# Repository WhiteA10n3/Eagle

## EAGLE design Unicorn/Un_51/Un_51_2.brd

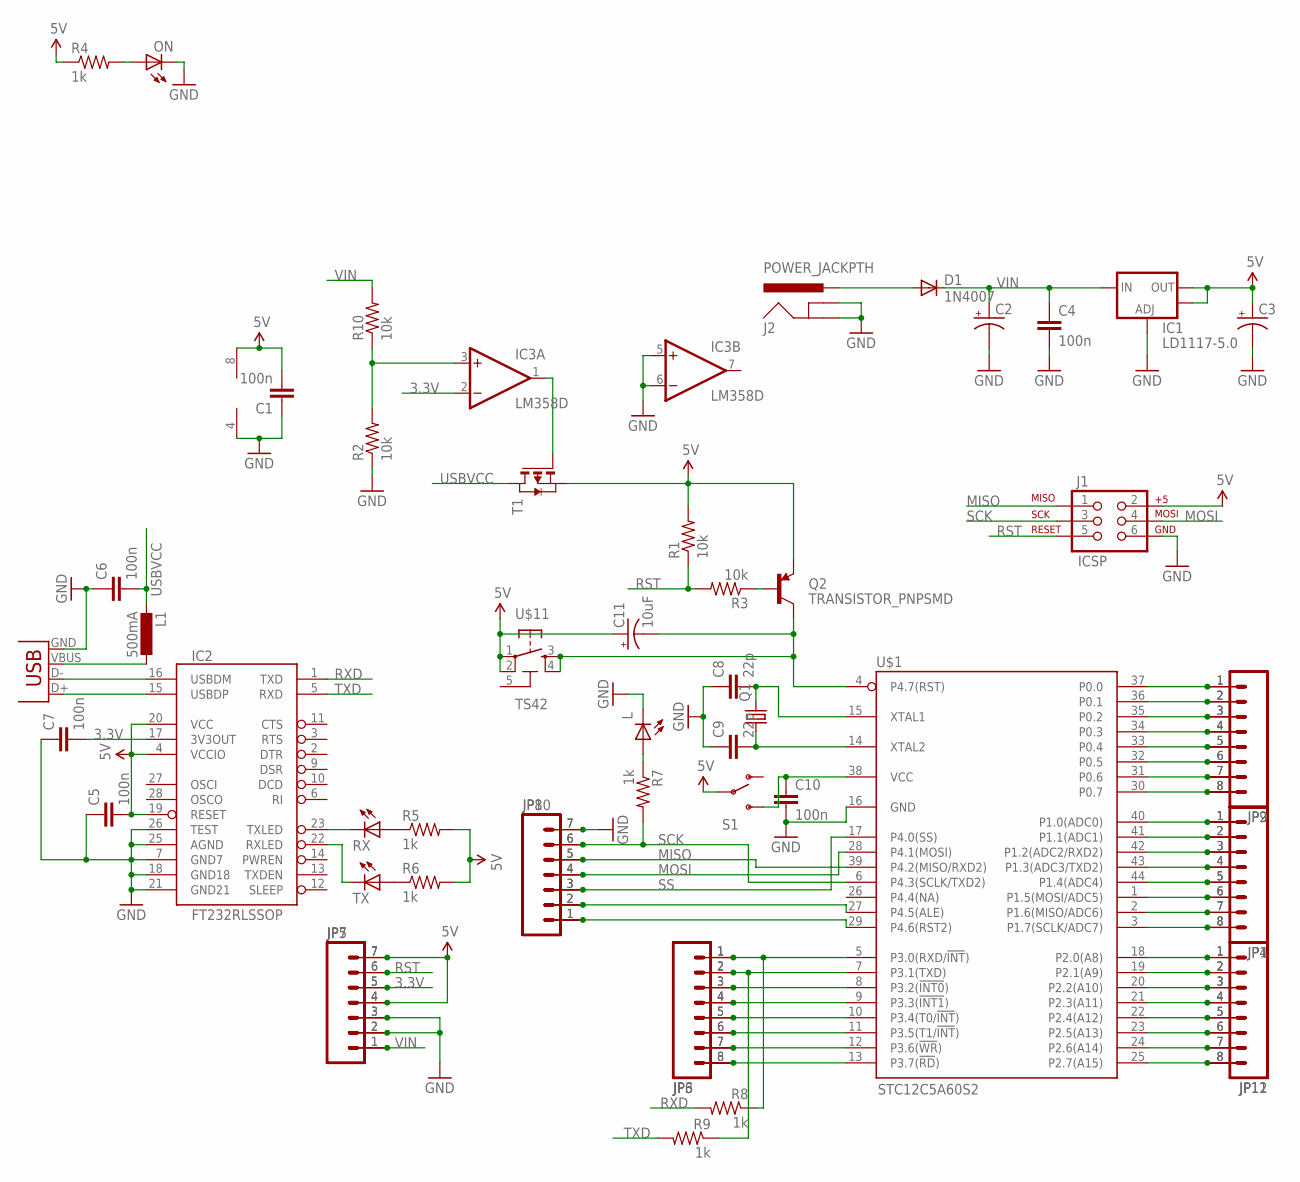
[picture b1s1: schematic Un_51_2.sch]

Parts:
C1, C4, C5, C6, C7, C10: 100n; 0603-CAP
C2, C3: CAP_POLD; PANASONIC_D
C8, C9: 22p; 0805
C11: 10uF; EIA3216
D1: 1N4007; SMB
IC1: LD1117-5.0; SOT223
IC2: FT232RLSSOP; SSOP28DB
IC3: LM358D; SO08
J1: ICSP; 2X3
J2: POWER_JACKPTH; POWER_JACK_PTH
JP1, JP2, JP4, JP9, JP11, JP12: M081X08; 1X08
JP3, JP6: M08; 1X08
JP5, JP7, JP8, JP10: M07; 1X07
L: LED0805; LED-0805
L1: 500mA; L1812
ON: LED0805; LED-0805
Q1: CRYSTALHC49US; HC49US
Q2: TRANSISTOR_PNPSMD; SOT23-3
R1, R2, R3, R10: 10k; 0805
R4, R5, R6, R7, R8, R9: 1k; 0805
RX: LED0805; LED-0805
S1: SWITCH-SPST; SWITCH-SPDT2
T1: PMOSSOT23; SOT-23
TX: LED0805; LED-0805
U$1: STC12C5A60S2; TQFP44
U$11: TS42
X1: USBPTH; USB-B-PTH

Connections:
3.3V: C7.2, IC2.17 (3V3OUT), IC3.2 (-IN), JP5.5, JP7.5
5V: C1.2, C3.+, C5.2, C11.A (+), IC1.2 (OUT), IC1.4 (OUT), IC2.4 (VCCIO), IC2.19 (RESET), IC2.20 (VCC), IC3.8 (V+), J1.2, JP5.4, JP5.7, JP7.4, JP7.7, Q2.2 (E), R1.2, R4.1, R5.2, R6.2, S1.2, T1.2 (S), U$11.1, U$11.2
A0: JP1.1, JP4.1, U$1.40 (P1.0(ADC0))
GND: C1.1, C2.-, C3.-, C4.2, C5.1, C6.1, C7.1, C8.1, C9.1, C10.2, IC1.1 (ADJ), IC2.7 (GND7), IC2.18 (GND18), IC2.21 (GND21), IC2.25 (AGND), IC2.26 (TEST), IC3.4 (V-), IC3.5 (+IN), IC3.6 (-IN), J1.6, J2.GND, J2.GNDBREAK, JP5.2, JP5.3, JP7.2, JP7.3, JP8.7, JP10.7, L.2 (C), ON.2 (C), R2.1, U$1.16 (GND), X1.GND
MISO: J1.1, JP8.5, JP10.5, U$1.39 (P4.2(MISO/RXD2))
MOSI: J1.4, JP8.4, JP10.4, U$1.28 (P4.1(MOSI))
unnamed: IC3.3 (+IN), R2.2, R10.1
unnamed: IC3.1 (OUT), T1.3 (G)
unnamed: L1.1, X1.VBUS
unnamed: D1.A, J2.PWR
unnamed: IC2.16 (USBDM), X1.D-
unnamed: IC2.15 (USBDP), X1.D+
unnamed: R5.1, RX.1 (A)
unnamed: R6.1, TX.1 (A)
unnamed: IC2.23 (TXLED), RX.2 (C)
unnamed: IC2.22 (RXLED), TX.2 (C)
unnamed: JP3.1, JP6.1, R8.1, U$1.5 (P3.0(RXD/!INT!))
unnamed: JP1.7, JP4.7, U$1.2 (P1.6(MISO/ADC6))
unnamed: JP1.8, JP4.8, U$1.3 (P1.7(SCLK/ADC7))
unnamed: L.1 (A), R7.1
unnamed: C10.1, S1.3 (S), U$1.38 (VCC)
unnamed: JP8.1, JP10.1, U$1.29 (P4.6(RST2))
unnamed: JP8.2, JP10.2, U$1.27 (P4.5(ALE))
unnamed: C11.C (-), Q2.3 (C), U$1.4 (P4.7(RST)), U$11.3, U$11.4
unnamed: Q2.1 (B), R3.1
unnamed: JP2.1, JP9.1, U$1.37 (P0.0)
unnamed: JP2.2, JP9.2, U$1.36 (P0.1)
unnamed: JP3.2, JP6.2, R9.1, U$1.7 (P3.1(TXD))
unnamed: JP3.3, JP6.3, U$1.8 (P3.2(!INT0!))
unnamed: JP3.4, JP6.4, U$1.9 (P3.3(!INT1!))
unnamed: JP3.5, JP6.5, U$1.10 (P3.4(T0/!INT!))
unnamed: JP3.6, JP6.6, U$1.11 (P3.5(T1/!INT!))
unnamed: JP3.7, JP6.7, U$1.12 (P3.6(!WR!))
unnamed: JP3.8, JP6.8, U$1.13 (P3.7(!RD!))
unnamed: JP1.2, JP4.2, U$1.41 (P1.1(ADC1))
unnamed: JP1.3, JP4.3, U$1.42 (P1.2(ADC2/RXD2))
unnamed: JP1.4, JP4.4, U$1.43 (P1.3(ADC3/TXD2))
unnamed: ON.1 (A), R4.2
unnamed: JP2.3, JP9.3, U$1.35 (P0.2)
unnamed: JP2.4, JP9.4, U$1.34 (P0.3)
unnamed: JP2.5, JP9.5, U$1.33 (P0.4)
unnamed: C8.2, Q1.2, U$1.15 (XTAL1)
unnamed: C9.2, Q1.1, U$1.14 (XTAL2)
unnamed: JP2.6, JP9.6, U$1.32 (P0.5)
unnamed: JP2.7, JP9.7, U$1.31 (P0.6)
unnamed: JP2.8, JP9.8, U$1.30 (P0.7)
unnamed: JP11.1, JP12.1, U$1.18 (P2.0(A8))
unnamed: JP11.2, JP12.2, U$1.19 (P2.1(A9))
unnamed: JP11.3, JP12.3, U$1.20 (P2.2(A10))
unnamed: JP11.4, JP12.4, U$1.21 (P2.3(A11))
unnamed: JP11.5, JP12.5, U$1.22 (P2.4(A12))
unnamed: JP11.6, JP12.6, U$1.23 (P2.5(A13))
unnamed: JP11.7, JP12.7, U$1.24 (P2.6(A14))
unnamed: JP11.8, JP12.8, U$1.25 (P2.7(A15))
RST: J1.5, JP5.6, JP7.6, R1.1, R3.2
RXD: IC2.1 (TXD), R8.2
SCK: J1.3, JP8.6, JP10.6, R7.2, U$1.6 (P4.3(SCLK/TXD2))
SCL: JP1.6, JP4.6, U$1.1 (P1.5(MOSI/ADC5))
SDA: JP1.5, JP4.5, U$1.44 (P1.4(ADC4))
SS: JP8.3, JP10.3, U$1.17 (P4.0(SS))
TXD: IC2.5 (RXD), R9.2
USBVCC: C6.2, L1.2, T1.1 (D)
VIN: C2.+, C4.1, D1.C, IC1.3 (IN), JP5.1, JP7.1, R10.2

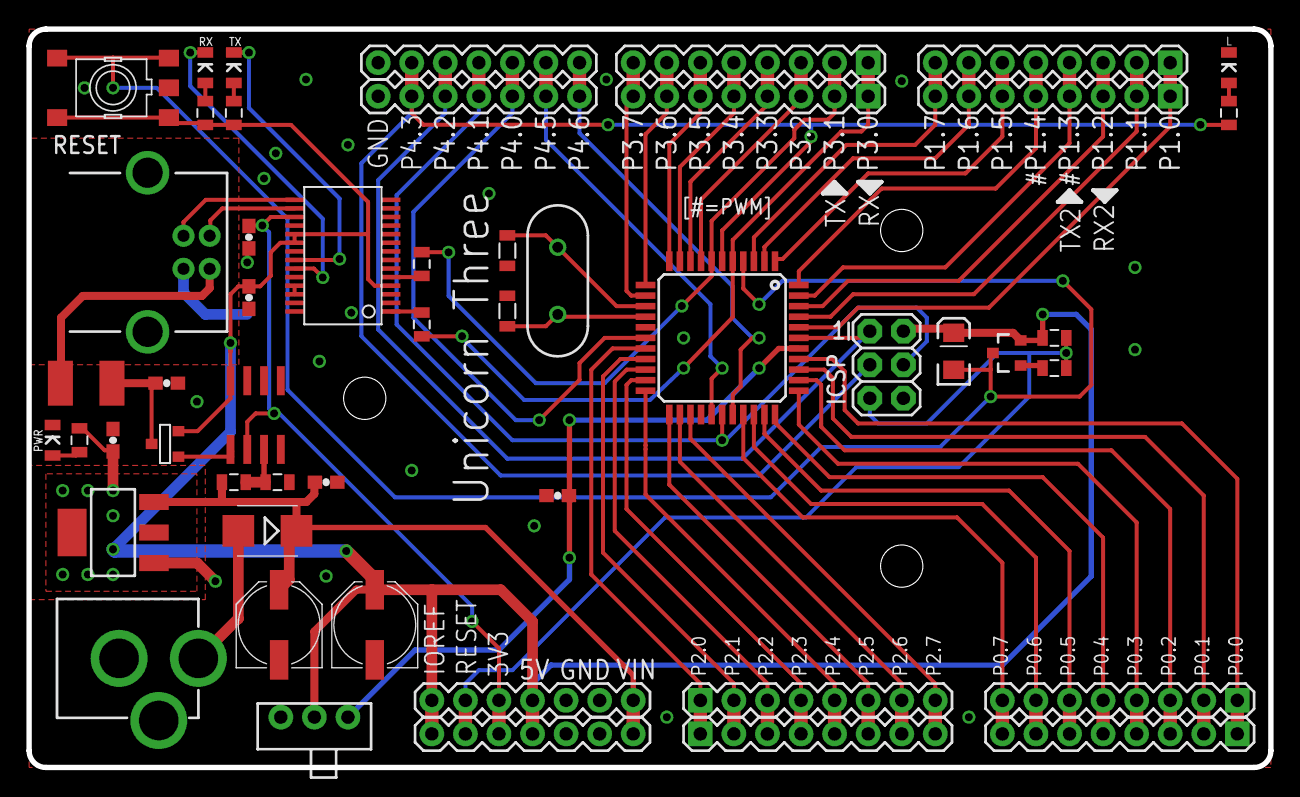
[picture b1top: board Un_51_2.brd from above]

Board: 2 copper layers, 94.0 x 55.9 mm, 51 parts (0 on the bottom side), 63 nets.

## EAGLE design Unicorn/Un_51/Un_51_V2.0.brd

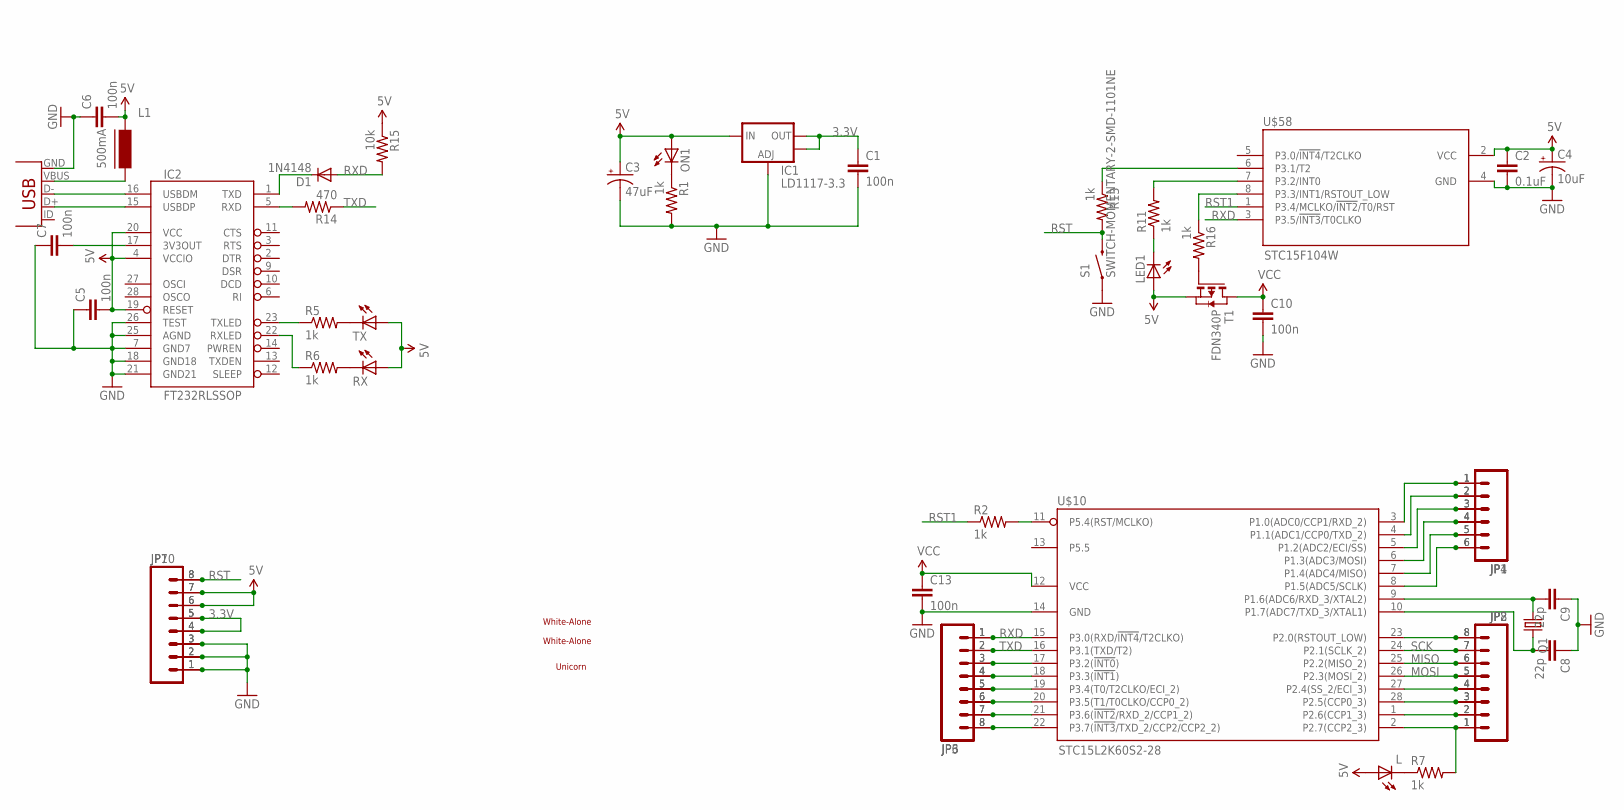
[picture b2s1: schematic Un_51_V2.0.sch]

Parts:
C1, C5, C6, C7, C10, C13: 100n; 0603-CAP
C2: 0.1uF; 0603-CAP
C3: 47uF; PANASONIC_D
C4: 10uF; EIA3216
C8, C9: 22p; 0603-CAP
D1: 1N4148; SOD-323
IC1: LD1117-3.3; SOT223
IC2: FT232RLSSOP; SSOP28DB
JP1, JP4: M06SIP; 1X06
JP2, JP3, JP6, JP7, JP8, JP10: M08; 1X08
L: LED0805; LED-0805
L1: 500mA; FB805
LED1: LED0805; LED-0805
ON1: LED0805; LED-0805
Q1: CRYSTALHC49US; HC49US
R1, R2, R5, R6, R7, R11, R13, R16: 1k; 0603-RES
R14: 470; 0603-RES
R15: 10k; 0603-RES
RX: LED0805; LED-0805
S1: SWITCH-MOMENTARY-2-SMD-1101NE; TACTILE-SWITCH-1101NE
T1: FDN340P; SOT-23
TX: LED0805; LED-0805
U$3: UNICORN_1
U$7, U$11: WHITE-ALONE_0
U$10: STC15L2K60S2-28; SO-28W
U$58: STC15F104W; SO08
X2: USBSMD; USB-MINIB

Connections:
3.3V: C1.1, IC1.2 (OUT), IC1.4 (OUT), JP7.4, JP7.5, JP10.4, JP10.5
5V: C2.1, C3.+, C4.A (+), C5.2, C6.2, IC1.3 (IN), IC2.4 (VCCIO), IC2.19 (RESET), IC2.20 (VCC), JP7.6, JP7.7, JP10.6, JP10.7, L.1 (A), L1.1, LED1.1 (A), ON1.1 (A), R15.1, RX.1 (A), T1.2 (S), TX.1 (A), U$58.2 (VCC)
GND: C1.2, C2.2, C3.-, C4.C (-), C5.1, C6.1, C7.1, C8.1, C9.1, C10.2, C13.2, IC1.1 (ADJ), IC2.7 (GND7), IC2.18 (GND18), IC2.21 (GND21), IC2.25 (AGND), IC2.26 (TEST), JP7.1, JP7.2, JP7.3, JP10.1, JP10.2, JP10.3, R1.2, S1.P$1 (1), U$10.14 (GND), U$58.4 (GND), X2.GND
MISO: JP2.6, JP8.6, U$10.25 (P2.2(MISO_2))
MOSI: JP2.5, JP8.5, U$10.26 (P2.3(MOSI_2))
unnamed: JP1.6, JP4.6, U$10.8 (P1.5(ADC5/SCLK))
unnamed: JP1.5, JP4.5, U$10.7 (P1.4(ADC4/MISO))
unnamed: L1.2, X2.VBUS
unnamed: LED1.2 (C), R11.1
unnamed: IC2.16 (USBDM), X2.D-
unnamed: IC2.15 (USBDP), X2.D+
unnamed: IC2.23 (TXLED), R5.1
unnamed: R5.2, TX.2 (C)
unnamed: R6.2, RX.2 (C)
unnamed: IC2.22 (RXLED), R6.1
unnamed: JP3.8, JP6.8, U$10.22 (P3.7(!INT3!/TXD_2/CCP2/CCP2_2))
unnamed: JP1.4, JP4.4, U$10.6 (P1.3(ADC3/MOSI))
unnamed: JP1.3, JP4.3, U$10.5 (P1.2(ADC2/ECI/SS))
unnamed: JP1.2, JP4.2, U$10.4 (P1.1(ADC1/CCP0/TXD_2))
unnamed: JP3.7, JP6.7, U$10.21 (P3.6(!INT2!/RXD_2/CCP1_2))
unnamed: JP2.8, JP8.8, U$10.23 (P2.0(RSTOUT_LOW))
unnamed: JP1.1, JP4.1, U$10.3 (P1.0(ADC0/CCP1/RXD_2))
unnamed: JP2.2, JP8.2, U$10.1 (P2.6(CCP1_3))
unnamed: JP2.1, JP8.1, R7.2, U$10.2 (P2.7(CCP2_3))
unnamed: R11.2, U$58.7 (P3.2/INT0)
unnamed: L.2 (C), R7.1
unnamed: C7.2, IC2.17 (3V3OUT)
unnamed: R2.2, U$10.11 (P5.4(RST/MCLKO))
unnamed: JP3.3, JP6.3, U$10.17 (P3.2(!INT0!))
unnamed: JP3.4, JP6.4, U$10.18 (P3.3(!INT1!))
unnamed: JP3.5, JP6.5, U$10.19 (P3.4(T0/T2CLKO/ECI_2))
unnamed: JP3.6, JP6.6, U$10.20 (P3.5(T1/T0CLKO/CCP0_2))
unnamed: R16.1, U$58.8 (P3.3/INT1/RSTOUT_LOW)
unnamed: JP2.3, JP8.3, U$10.28 (P2.5(CCP0_3))
unnamed: ON1.2 (C), R1.1
unnamed: R13.1, U$58.6 (P3.1/T2)
unnamed: IC2.5 (RXD), R14.2
unnamed: D1.1 (C), IC2.1 (TXD)
unnamed: C8.2, Q1.2, U$10.10 (P1.7(ADC7/TXD_3/XTAL1))
unnamed: C9.2, Q1.1, U$10.9 (P1.6(ADC6/RXD_3/XTAL2))
unnamed: R16.2, T1.3 (G)
unnamed: JP2.4, JP8.4, U$10.27 (P2.4(SS_2/ECI_3))
RST: JP7.8, JP10.8, R13.2, S1.P$2 (2)
RST1: R2.1, U$58.1 (P3.4/MCLKO/!INT2!/T0/RST)
RXD: D1.2 (A), JP3.1, JP6.1, R15.2, U$10.15 (P3.0(RXD/!INT4!/T2CLKO)), U$58.3 (P3.5/!INT3!/T0CLKO)
SCK: JP2.7, JP8.7, U$10.24 (P2.1(SCLK_2))
TXD: JP3.2, JP6.2, R14.1, U$10.16 (P3.1(TXD/T2))
VCC: C10.1, C13.1, T1.1 (D), U$10.12 (VCC)

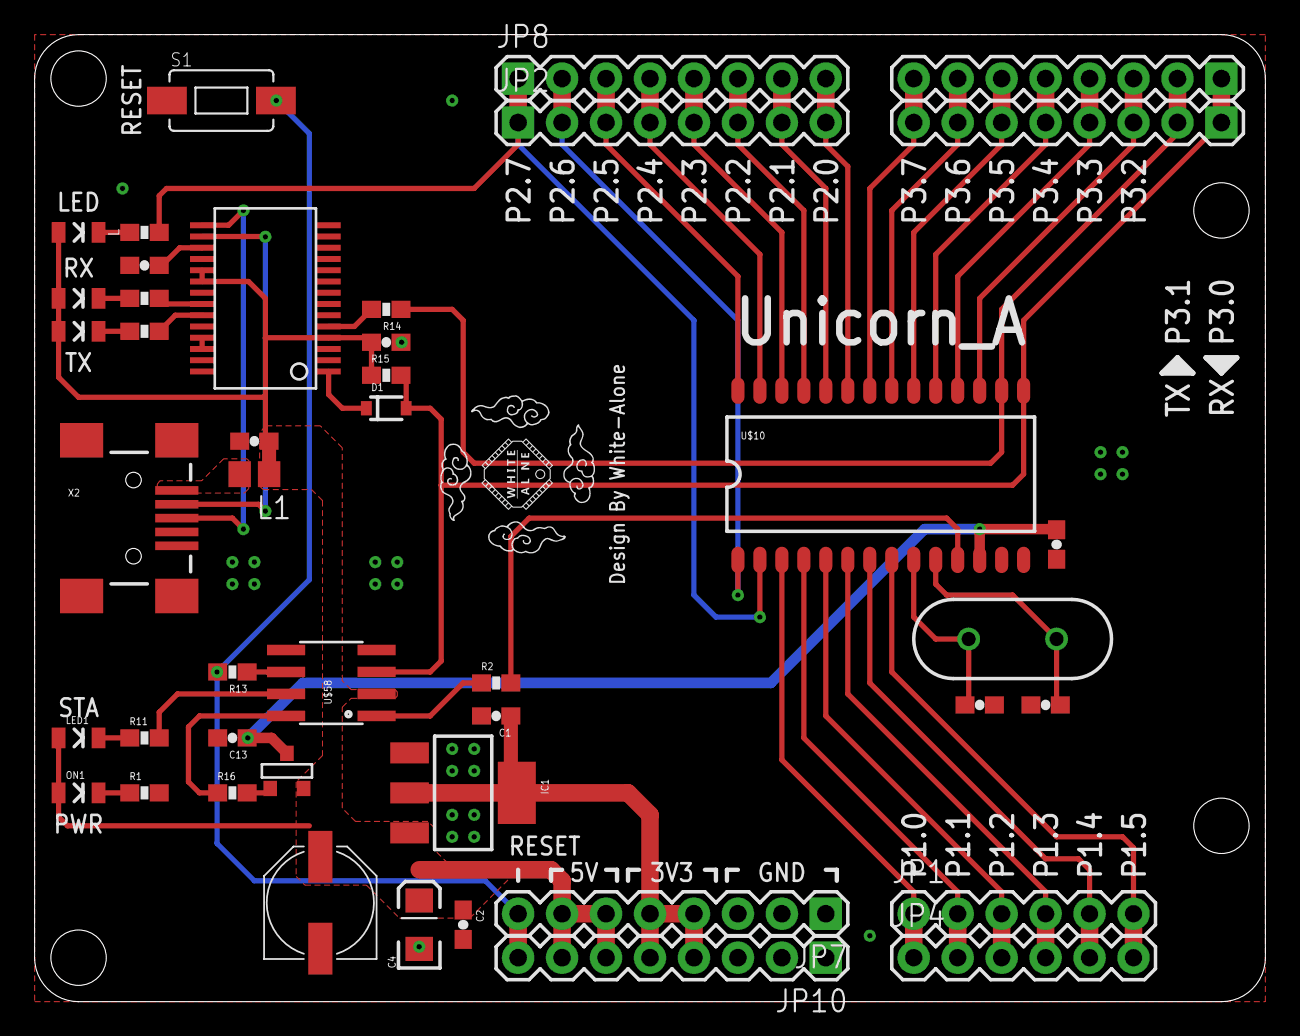
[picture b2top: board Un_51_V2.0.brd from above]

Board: 2 copper layers, 71.1 x 55.9 mm, 47 parts (1 on the bottom side), 48 nets.

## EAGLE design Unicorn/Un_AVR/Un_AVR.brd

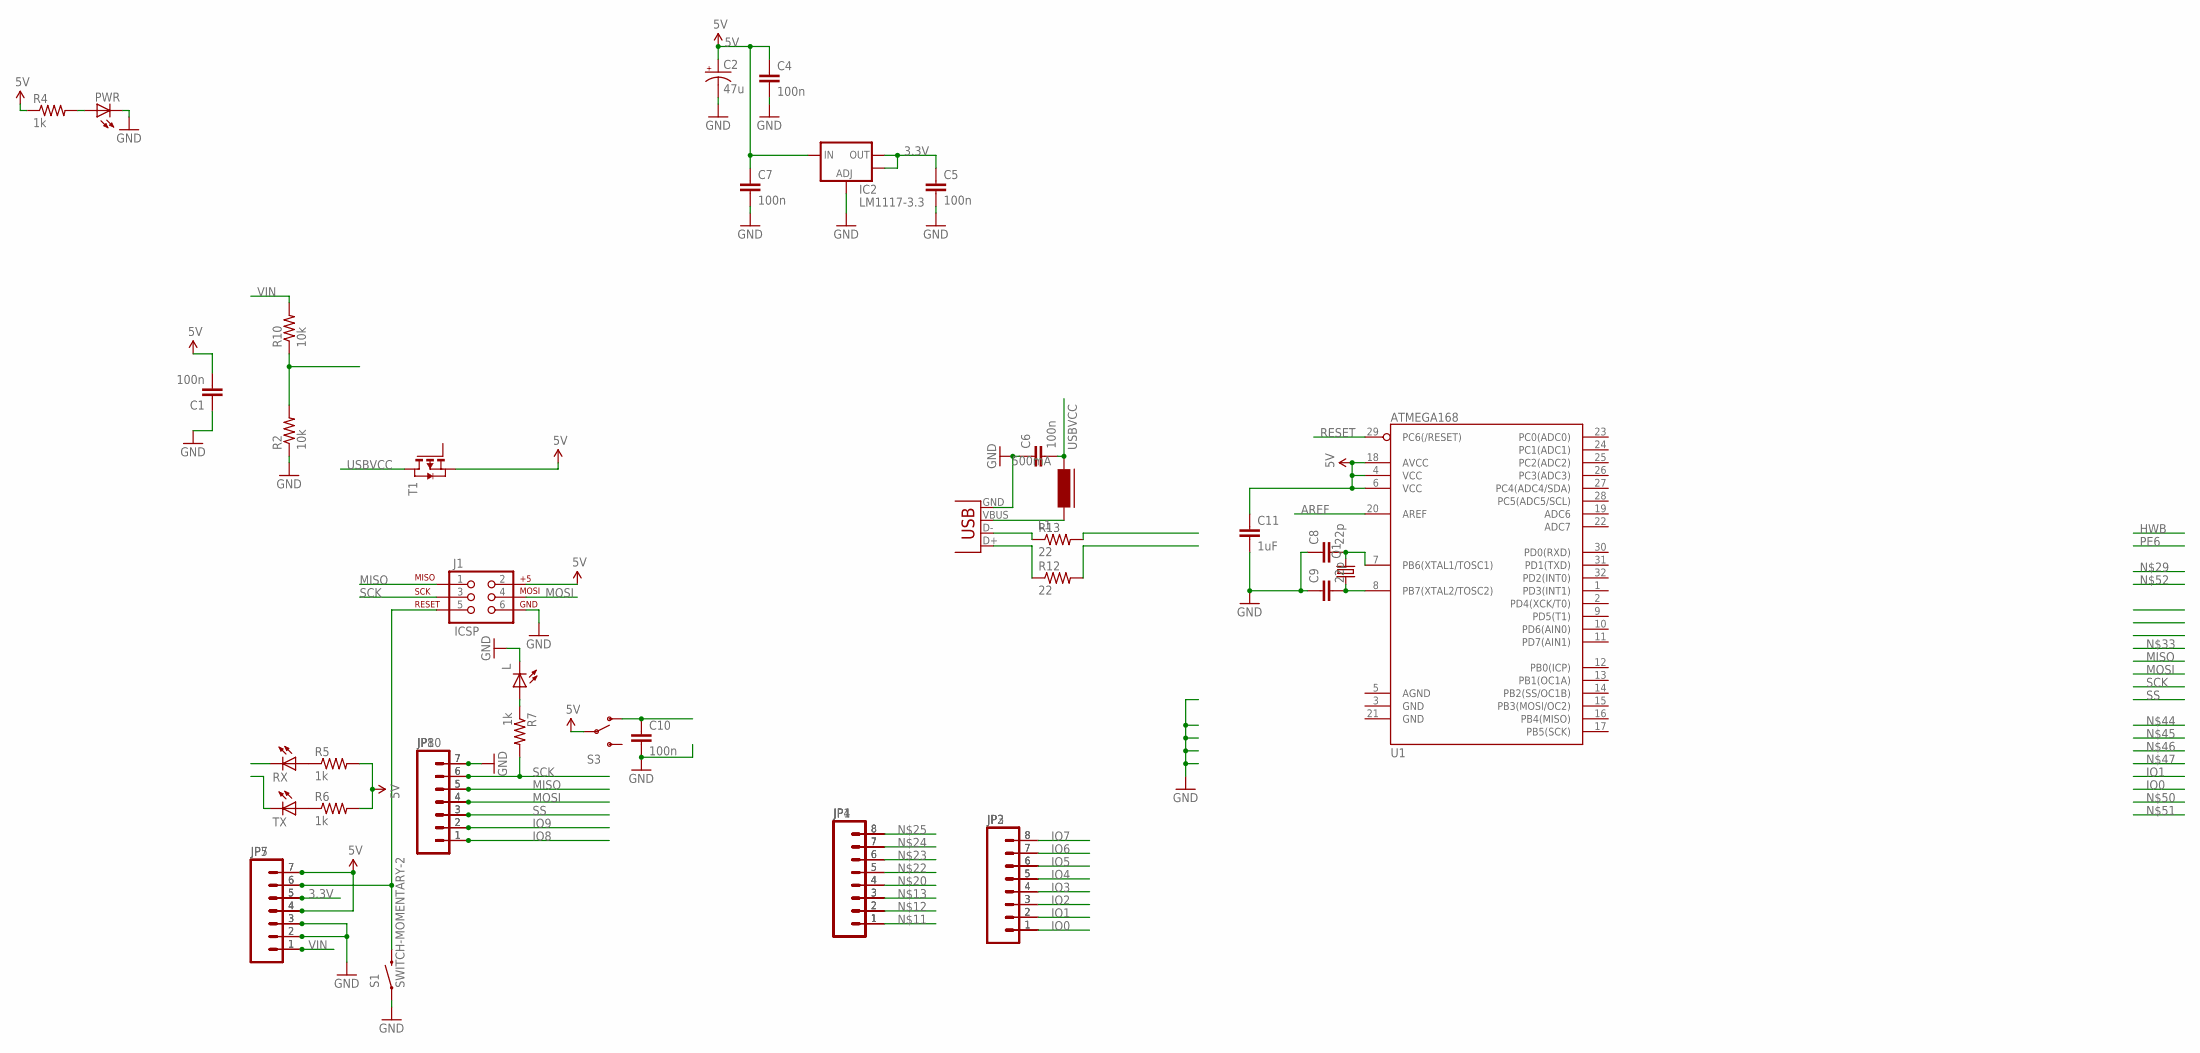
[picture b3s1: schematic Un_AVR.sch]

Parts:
C1, C4, C5, C6, C7, C10: 100n; 0603-CAP
C2: 47u; PANASONIC_D
C8, C9: 22p; 0603-CAP
C11: 1uF; 0603-CAP
IC2: LM1117-3.3; SOT223
J1: ICSP; 2X3
JP1, JP2, JP3, JP4: M081X08; 1X08
JP5, JP7, JP8, JP10: M07; 1X07
L: LED0805; LED-0805
L1: 500mA; FB805
PWR: LED0805; LED-0805
Q1: CRYSTALHC49US; HC49US
R2, R10: 10k; 0805
R4, R5, R6, R7: 1k; 0805
R12, R13: 22; 0805
RX: LED0805; LED-0805
S1: SWITCH-MOMENTARY-2; TACTILE_SWITCH_TALL
S3: SWITCH-SPSTPTH; SWITCH-SPDT
T1: PMOSSOT23; SOT-23
TX: LED0805; LED-0805
U1: ATMEGA168; TQFP32-08
X1: USBSMD; USB-MINIB

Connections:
3.3V: C5.1, IC2.2 (OUT), IC2.4 (OUT), JP5.5, JP7.5
5V: C1.2, C2.+, C4.1, C7.1, C11.1, IC2.3 (IN), J1.2, JP5.4, JP5.7, JP7.4, JP7.7, R4.1, R5.2, R6.2, S3.2, T1.2 (S), U1.4 (VCC), U1.6 (VCC), U1.18 (AVCC)
AREF: U1.20 (AREF)
GND: C1.1, C2.-, C4.2, C5.2, C6.1, C7.2, C8.1, C9.1, C10.2, C11.2, IC2.1 (ADJ), J1.6, JP5.2, JP5.3, JP7.2, JP7.3, JP8.7, JP10.7, L.2 (C), PWR.2 (C), R2.1, S1.A2 (1), X1.GND
IO0: JP2.1, JP3.1
IO1: JP2.2, JP3.2
IO2: JP2.3, JP3.3
IO3: JP2.4, JP3.4
IO4: JP2.5, JP3.5
IO5: JP2.6, JP3.6
IO6: JP2.7, JP3.7
IO7: JP2.8, JP3.8
IO8: JP8.1, JP10.1
IO9: JP8.2, JP10.2
MISO: J1.1, JP8.5, JP10.5
MOSI: J1.4, JP8.4, JP10.4
unnamed: R2.2, R10.1
unnamed: L1.1, X1.VBUS
unnamed: R13.1, X1.D-
unnamed: R5.1, RX.1 (A)
unnamed: R6.1, TX.1 (A)
unnamed: JP1.1, JP4.1
unnamed: JP1.2, JP4.2
unnamed: JP1.3, JP4.3
unnamed: L.1 (A), R7.1
unnamed: C10.1, S3.1 (O)
unnamed: R12.1, X1.D+
unnamed: JP1.4, JP4.4
unnamed: JP1.5, JP4.5
unnamed: JP1.6, JP4.6
unnamed: JP1.7, JP4.7
unnamed: JP1.8, JP4.8
unnamed: PWR.1 (A), R4.2
unnamed: J1.5, JP5.6, JP7.6, S1.B2 (2)
unnamed: C8.2, Q1.2, U1.7 (PB6(XTAL1/TOSC1))
unnamed: C9.2, Q1.1
RESET: U1.29 (PC6(/RESET))
SCK: J1.3, JP8.6, JP10.6, R7.2
SS: JP8.3, JP10.3
USBVCC: C6.2, L1.2, T1.1 (D)
VIN: JP5.1, JP7.1, R10.2

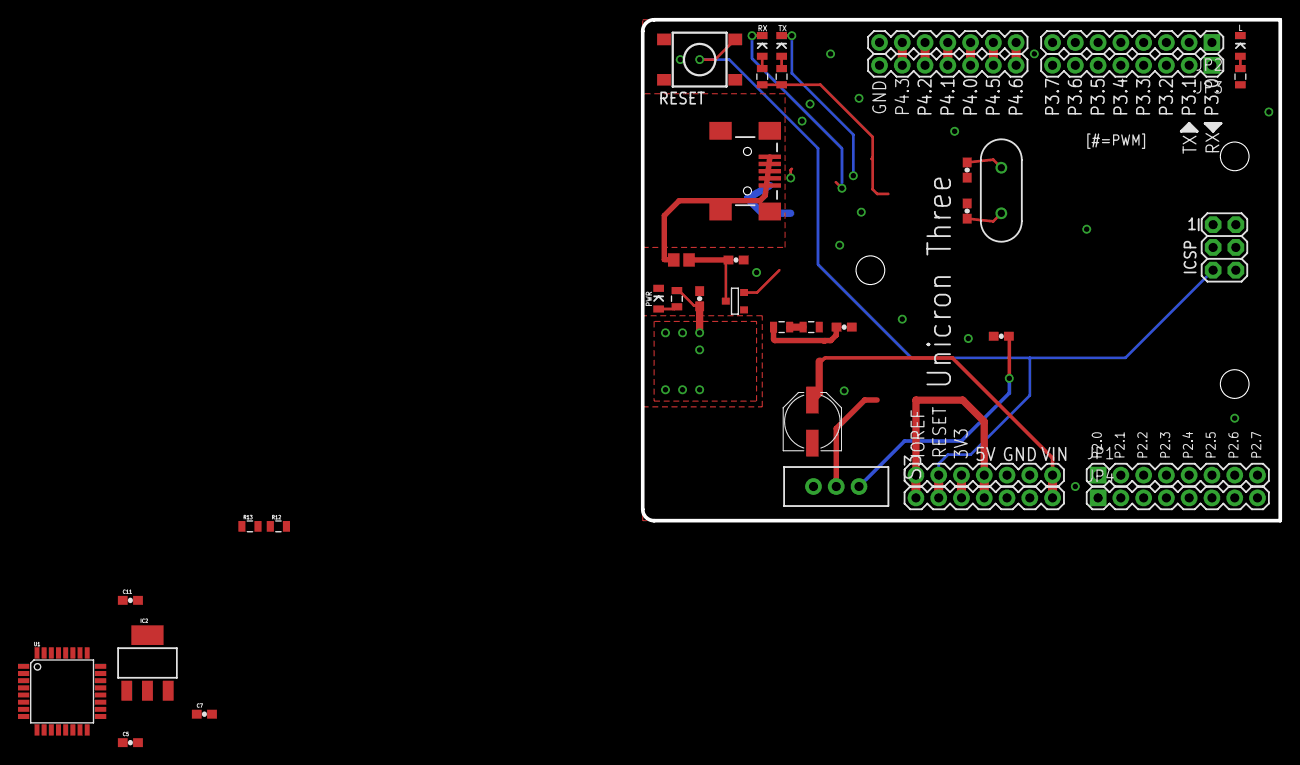
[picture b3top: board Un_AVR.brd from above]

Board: 2 copper layers, 71.1 x 55.9 mm, 39 parts (0 on the bottom side), 39 nets.

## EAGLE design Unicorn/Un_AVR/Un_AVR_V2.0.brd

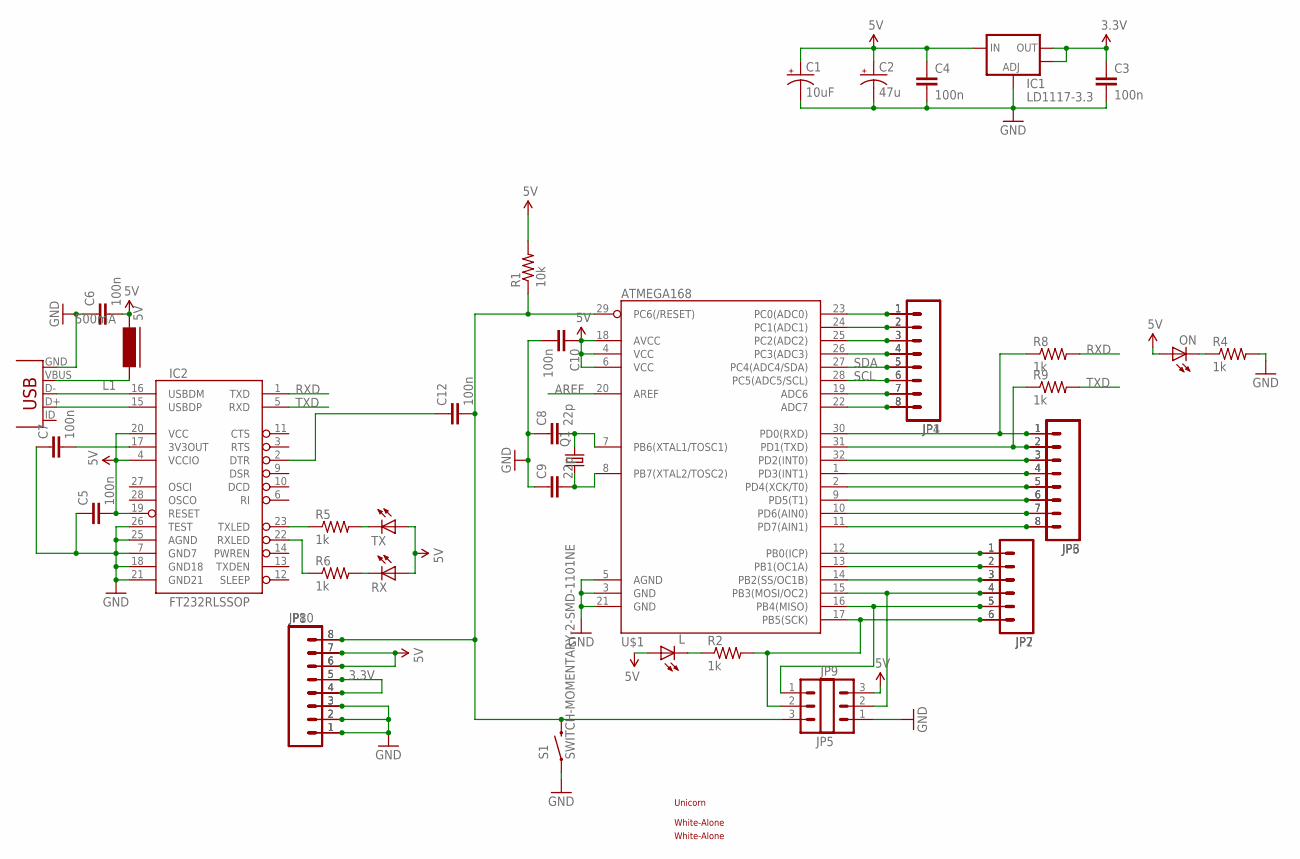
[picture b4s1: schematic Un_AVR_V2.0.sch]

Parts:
C1: 10uF; EIA3216
C2: 47u; PANASONIC_D
C3, C4, C5, C6, C7, C10, C12: 100n; 0603-CAP
C8, C9: 22p; 0603-CAP
IC1: LD1117-3.3; SOT223
IC2: FT232RLSSOP; SSOP28DB
JP1, JP4: M081X08; 1X08
JP2, JP7: M06SIP; 1X06
JP3, JP6, JP8, JP10: M08; 1X08
JP5, JP9: M03PTH; 1X03
L: LED0805; LED-0805
L1: 500mA; FB805
ON: LED0805; LED-0805
Q1: CRYSTALHC49US; HC49US
R1: 10k; 0603-RES
R2, R4, R5, R6, R8, R9: 1k; 0603-RES
RX: LED0805; LED-0805
S1: SWITCH-MOMENTARY-2-SMD-1101NE; TACTILE-SWITCH-1101NE
TX: LED0805; LED-0805
U$1: ATMEGA168; TQFP32-08
U$4: UNICORN_1
U$13, U$14: WHITE-ALONE_0
U$16: USB_5-SMD; USB-MINIB

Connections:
3.3V: C3.1, IC1.2 (OUT), IC1.4 (OUT), JP8.4, JP8.5, JP10.4, JP10.5
5V: C1.A (+), C2.+, C4.1, C5.2, C6.2, C10.1, IC1.3 (IN), IC2.4 (VCCIO), IC2.19 (RESET), IC2.20 (VCC), JP8.6, JP8.7, JP9.3, JP10.6, JP10.7, L.1 (A), L1.2, ON.1 (A), R1.2, RX.1 (A), TX.1 (A), U$1.4 (VCC), U$1.6 (VCC), U$1.18 (AVCC)
A0: JP1.1, JP4.1, U$1.23 (PC0(ADC0))
AREF: U$1.20 (AREF)
GND: C1.C (-), C2.-, C3.2, C4.2, C5.1, C6.1, C7.1, C8.1, C9.1, C10.2, IC1.1 (ADJ), IC2.7 (GND7), IC2.18 (GND18), IC2.21 (GND21), IC2.25 (AGND), IC2.26 (TEST), JP8.1, JP8.2, JP8.3, JP9.1, JP10.1, JP10.2, JP10.3, R4.2, S1.P$1 (1), U$1.3 (GND), U$1.5 (AGND), U$1.21 (GND), U$16.GND
IO0: JP3.1, JP6.1, R8.1, U$1.30 (PD0(RXD))
unnamed: C7.2, IC2.17 (3V3OUT)
unnamed: IC2.23 (TXLED), R5.1
unnamed: L1.1, U$16.VBUS
unnamed: R5.2, TX.2 (C)
unnamed: IC2.16 (USBDM), U$16.D-
unnamed: IC2.15 (USBDP), U$16.D+
unnamed: R6.2, RX.2 (C)
unnamed: ON.2 (C), R4.1
unnamed: L.2 (C), R2.1
unnamed: IC2.22 (RXLED), R6.1
unnamed: JP1.7, JP4.7, U$1.19 (ADC6)
unnamed: JP1.8, JP4.8, U$1.22 (ADC7)
unnamed: C12.2, JP5.3, JP8.8, JP10.8, R1.1, S1.P$2 (2), U$1.29 (PC6(/RESET))
unnamed: C12.1, IC2.2 (DTR)
unnamed: JP2.1, JP7.1, U$1.12 (PB0(ICP))
unnamed: JP2.2, JP7.2, U$1.13 (PB1(OC1A))
unnamed: JP2.3, JP7.3, U$1.14 (PB2(SS/OC1B))
unnamed: JP2.4, JP7.4, JP9.2, U$1.15 (PB3(MOSI/OC2))
unnamed: JP2.5, JP5.1, JP7.5, U$1.16 (PB4(MISO))
unnamed: JP3.2, JP6.2, R9.1, U$1.31 (PD1(TXD))
unnamed: JP3.3, JP6.3, U$1.32 (PD2(INT0))
unnamed: JP3.4, JP6.4, U$1.1 (PD3(INT1))
unnamed: JP3.5, JP6.5, U$1.2 (PD4(XCK/T0))
unnamed: JP3.6, JP6.6, U$1.9 (PD5(T1))
unnamed: JP3.7, JP6.7, U$1.10 (PD6(AIN0))
unnamed: JP3.8, JP6.8, U$1.11 (PD7(AIN1))
unnamed: JP1.2, JP4.2, U$1.24 (PC1(ADC1))
unnamed: JP1.3, JP4.3, U$1.25 (PC2(ADC2))
unnamed: JP1.4, JP4.4, U$1.26 (PC3(ADC3))
unnamed: C8.2, Q1.2, U$1.7 (PB6(XTAL1/TOSC1))
unnamed: C9.2, Q1.1, U$1.8 (PB7(XTAL2/TOSC2))
RXD: IC2.1 (TXD), R8.2
SCK: JP2.6, JP5.2, JP7.6, R2.2, U$1.17 (PB5(SCK))
SCL: JP1.6, JP4.6, U$1.28 (PC5(ADC5/SCL))
SDA: JP1.5, JP4.5, U$1.27 (PC4(ADC4/SDA))
TXD: IC2.5 (RXD), R9.2

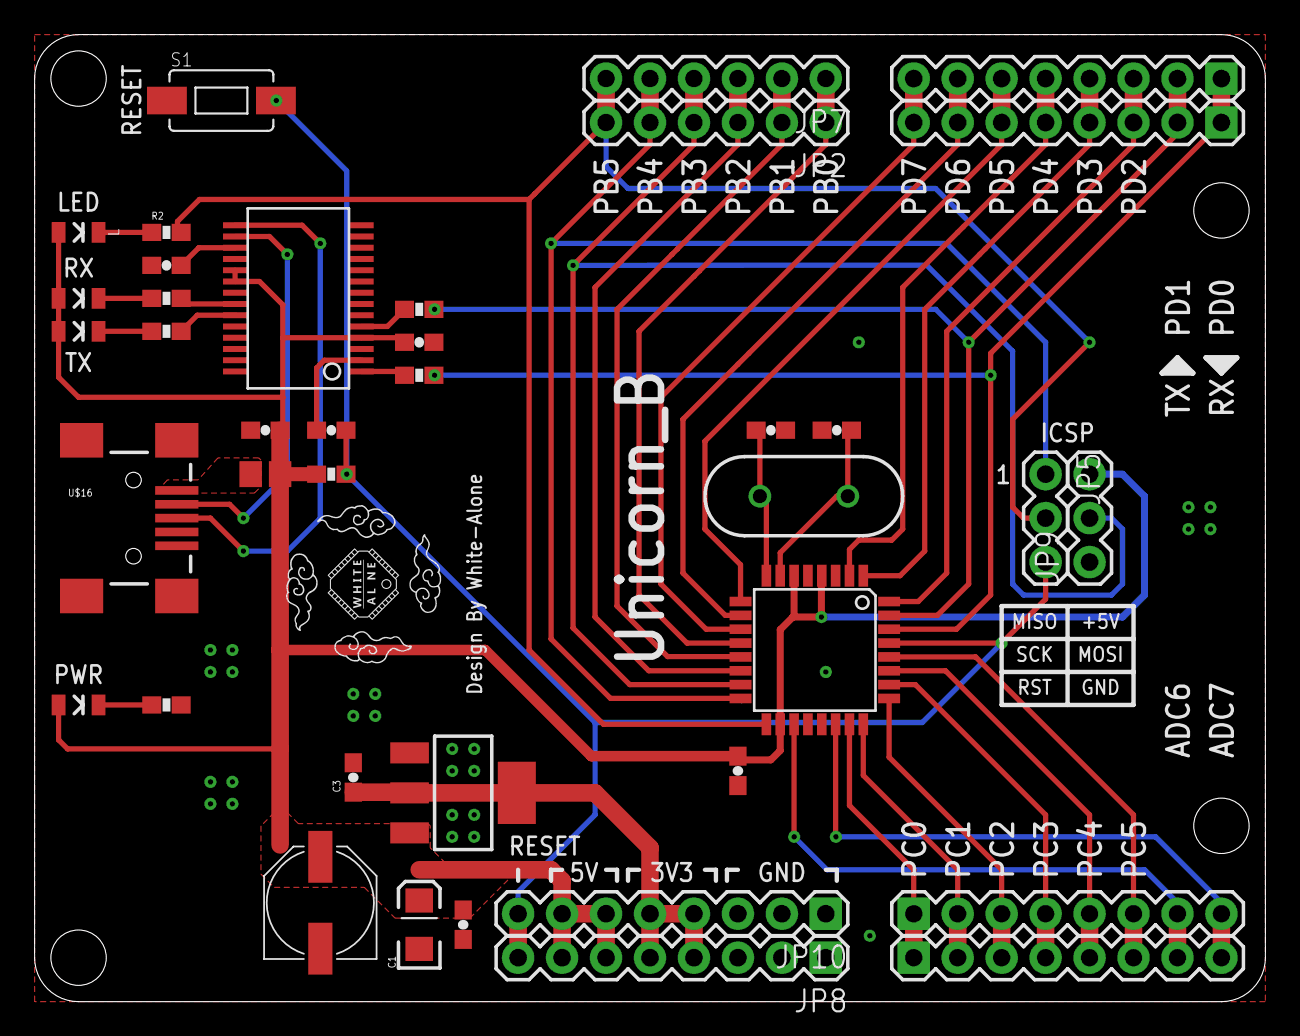
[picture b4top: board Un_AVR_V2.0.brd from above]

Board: 2 copper layers, 71.1 x 55.9 mm, 42 parts (1 on the bottom side), 41 nets.

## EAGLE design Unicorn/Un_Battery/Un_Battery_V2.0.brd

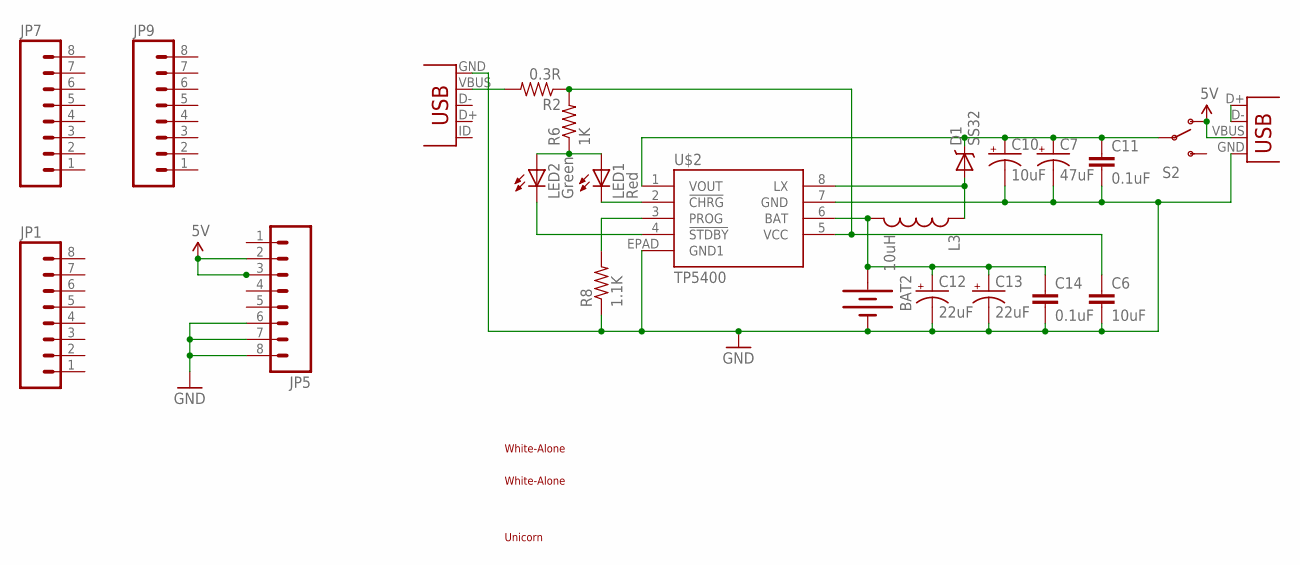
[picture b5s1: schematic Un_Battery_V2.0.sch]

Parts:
BAT2: BATTERYLIPO; BATTERY-LIPO
C6: 10uF; 1206
C7: 47uF; PANASONIC_D
C10: 10uF; EIA3216
C11, C14: 0.1uF; 1206
C12, C13: 22uF; EIA3216
D1: SS32; SMA-DIODE
JP1, JP5, JP7, JP9: M081X08; 1X08
L3: 10uH; CR75
LED1: Red; LED-0805
LED2: Green; LED-0805
R2: 0.3R; 1206
R6: 1K; 0805
R8: 1.1K; 0805
S2: SWITCH-SPST; SWITCH-SPDT2
U$2: TP5400; SO08-EPAD
U$4, U$5: WHITE-ALONE_2
U$6: USB_5-SMD; USB-MINIB
U$7: UNICORN_1
X2: USB-A-S

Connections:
5V: JP5.2, JP5.3, S2.1 (O), X2.VBUS
GND: BAT2.-, C6.2, C7.-, C10.C (-), C11.2, C12.C (-), C13.C (-), C14.2, JP5.6, JP5.7, JP5.8, R8.1, U$2.7 (GND), U$2.EPAD (GND1), U$6.GND, X2.GND
unnamed: R2.2, U$6.VBUS
unnamed: C6.1, R2.1, R6.2, U$2.5 (VCC)
unnamed: LED1.1 (A), LED2.1 (A), R6.1
unnamed: LED2.2 (C), U$2.4 (!STDBY)
unnamed: LED1.2 (C), U$2.2 (!CHRG)
unnamed: C7.+, C10.A (+), C11.1, D1.C, S2.2, U$2.1 (VOUT)
unnamed: R8.2, U$2.3 (PROG)
unnamed: D1.A, L3.P$1 (1), U$2.8 (LX)
unnamed: X2.D+, X2.D-
unnamed: BAT2.+, C12.A (+), C13.A (+), C14.1, L3.P$2 (2), U$2.6 (BAT)

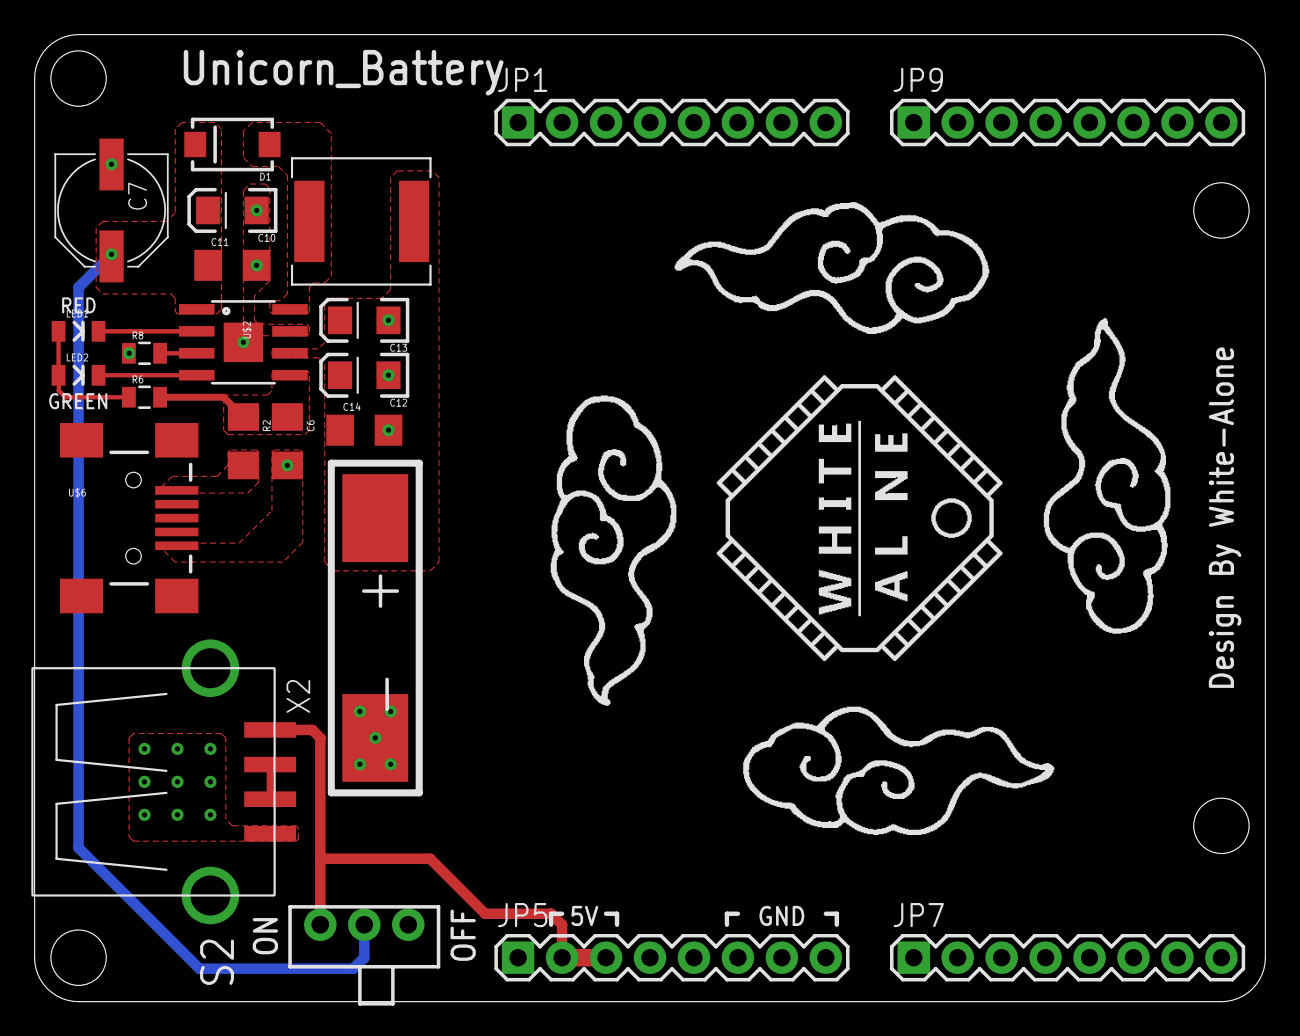
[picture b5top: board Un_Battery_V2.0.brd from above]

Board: 2 copper layers, 71.1 x 55.9 mm, 26 parts (1 on the bottom side), 12 nets.

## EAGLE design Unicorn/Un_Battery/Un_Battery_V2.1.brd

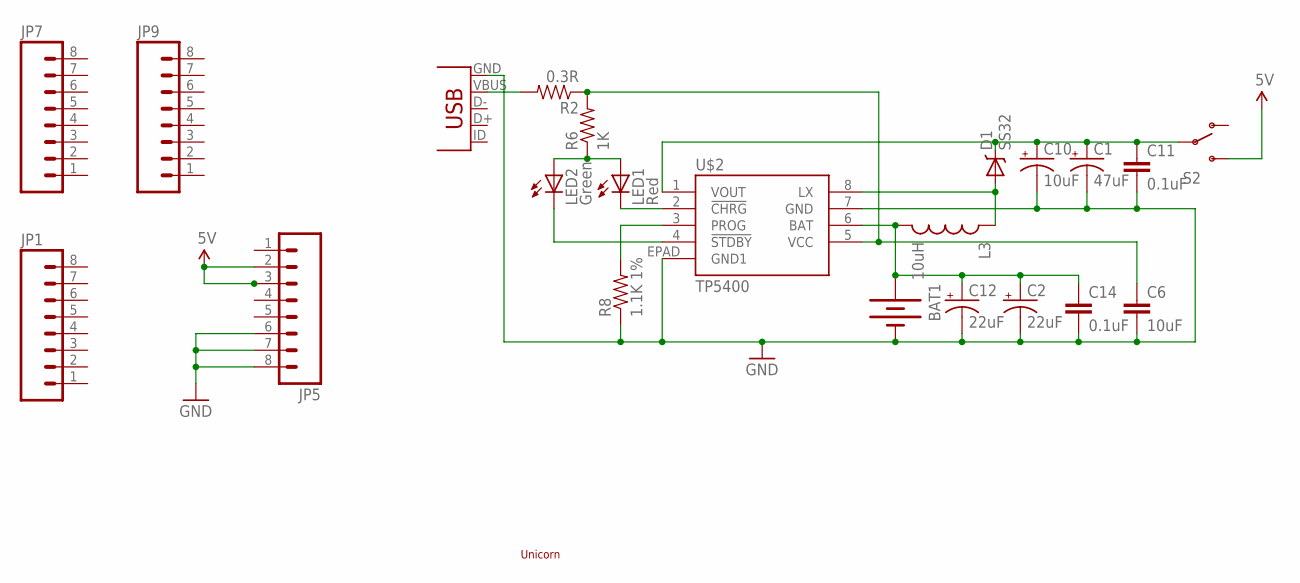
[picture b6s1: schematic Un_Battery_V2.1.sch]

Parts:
BAT1: BATTERYLIPO2; BATTERY-LIPO2
C1: 47uF; EIA3216
C2, C12: 22uF; EIA3216
C6: 10uF; 1206
C10: 10uF; EIA3216
C11, C14: 0.1uF; 0603-CAP
D1: SS32; SMA-DIODE
JP1, JP5, JP7, JP9: M081X08; 1X08
L3: 10uH; CR32
LED1: Red; LED-0603
LED2: Green; LED-0603
R2: 0.3R; 1206
R6: 1K; 0603-RES
R8: 1.1K 1%; 0603-RES
S2: SWITCH-SPST; SWITCH-SPDT2
U$2: TP5400; SO08-EPAD
U$6: USB_5-SMD; USB-MINIB
U$7: UNICORN_1

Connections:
5V: JP5.2, JP5.3, S2.3 (S)
GND: BAT1.-, C1.C (-), C2.C (-), C6.2, C10.C (-), C11.2, C12.C (-), C14.2, JP5.6, JP5.7, JP5.8, R8.1, U$2.7 (GND), U$2.EPAD (GND1), U$6.GND
unnamed: R2.2, U$6.VBUS
unnamed: C6.1, R2.1, R6.2, U$2.5 (VCC)
unnamed: LED1.A, LED2.A, R6.1
unnamed: LED2.C, U$2.4 (!STDBY)
unnamed: LED1.C, U$2.2 (!CHRG)
unnamed: C1.A (+), C10.A (+), C11.1, D1.C, S2.2, U$2.1 (VOUT)
unnamed: R8.2, U$2.3 (PROG)
unnamed: D1.A, L3.P$1 (1), U$2.8 (LX)
unnamed: BAT1.+, C2.A (+), C12.A (+), C14.1, L3.P$2 (2), U$2.6 (BAT)

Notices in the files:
parts and their libraries:
1SparkFun: Licensing: CC v3.0 Share-Alike You are welcome to use this library for commercial purposes.
